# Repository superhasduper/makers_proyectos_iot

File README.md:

# makers_proyectos_iot
proyecto de maker proyectos de techtalents de iot con arduino 
if you want to access the pcb files use kicad
latest pcb is finished

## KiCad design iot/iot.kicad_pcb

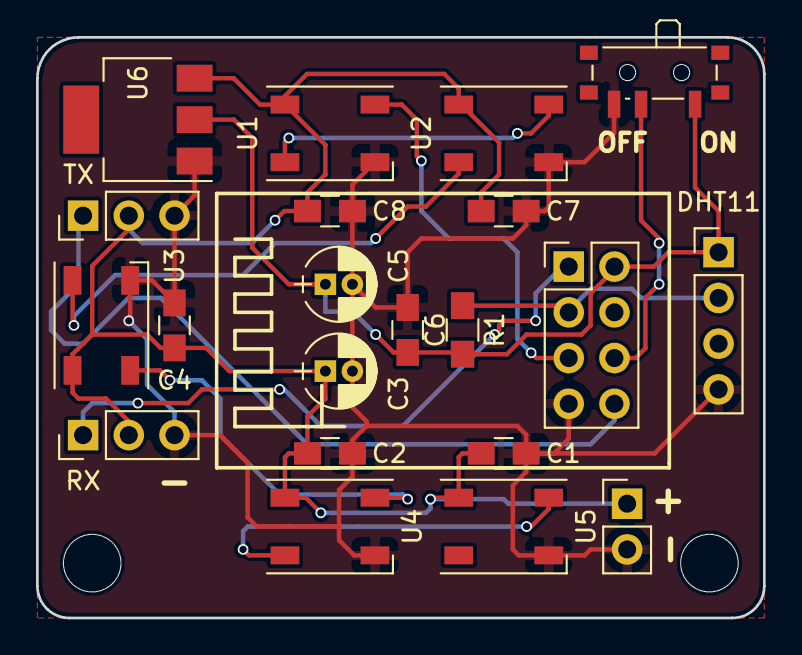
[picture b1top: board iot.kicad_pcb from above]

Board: 2 copper layers, 40.4 x 32.3 mm, 21 parts (0 on the bottom side), 12 nets.

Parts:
C1, C2, C4, C6, C7, C8: 100n; C_0805_HandSoldering
C3: 10uF; CP_Radial_D4.0mm_P1.50mm
C5: 22uF; CP_Radial_D4.0mm_P1.50mm
DHT11: DHT11; Pin_Header_Straight_1x04_Pitch2.54mm
J1: Conn_02x04_Top_Bottom; Pin_Header_Straight_2x04_Pitch2.54mm
J2: Conn_01x02; Pin_Header_Straight_1x02_Pitch2.54mm
R1: 4k7; R_0805_HandSoldering
RX: Conn_01x03; Pin_Header_Straight_1x03_Pitch2.54mm
SW1: SW_Push_SPDT; SW_SPDT_PCM12
TX: Conn_01x03; Pin_Header_Straight_1x03_Pitch2.54mm
U1, U2, U3, U4, U5: WS2812b; LED_WS2812B-PLCC4
U6: LM1117-3.3; SOT-223

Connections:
+3V3: C5.1, C6.1, DHT11.1, J1.5, R1.1, SW1.1, U6.2
+5V: C1.1, C2.1, C3.1, C4.1, C7.1, C8.1, J2.1, RX.2, TX.2, U1.1, U2.1, U3.1, U4.1, U5.1, U6.3
/CH_PD: J1.7, SW1.2
/GPIO_0: DHT11.2, J1.2, R1.2
/GPIO_2: J1.3, U1.4
/RX: J1.1, RX.1
/TX: J1.8, TX.1
GND: C1.2, C2.2, C3.2, C4.2, C5.2, C6.2, C7.2, C8.2, DHT11.4, J1.4, J2.2, RX.3, SW1.3, TX.3, U1.3, U2.3, U3.3, U4.3, U5.3, U6.1
unnamed: U1.2, U2.4
unnamed: U2.2, U3.4
unnamed: U3.2, U4.4
unnamed: U4.2, U5.4

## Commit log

2018-02-24 Created initial.gitignore
    created initial .gitignore with passwords and vscode settings files
2018-02-24 basic structure setup
    basic structure setup with php, css and javascript files
2018-03-03 design of part of the circuit
    In this commit I did part of the design of the schematics and designed some of the symbols of the components needed for the project in kicad
2018-03-17 finished
    in this commit the pcb is finished
2018-04-07 polished
    I polished the final design to be more aesthetic
2018-04-07 polished fixed
    sorry I uploaded the wrong file for polished this is the correct one I hope
